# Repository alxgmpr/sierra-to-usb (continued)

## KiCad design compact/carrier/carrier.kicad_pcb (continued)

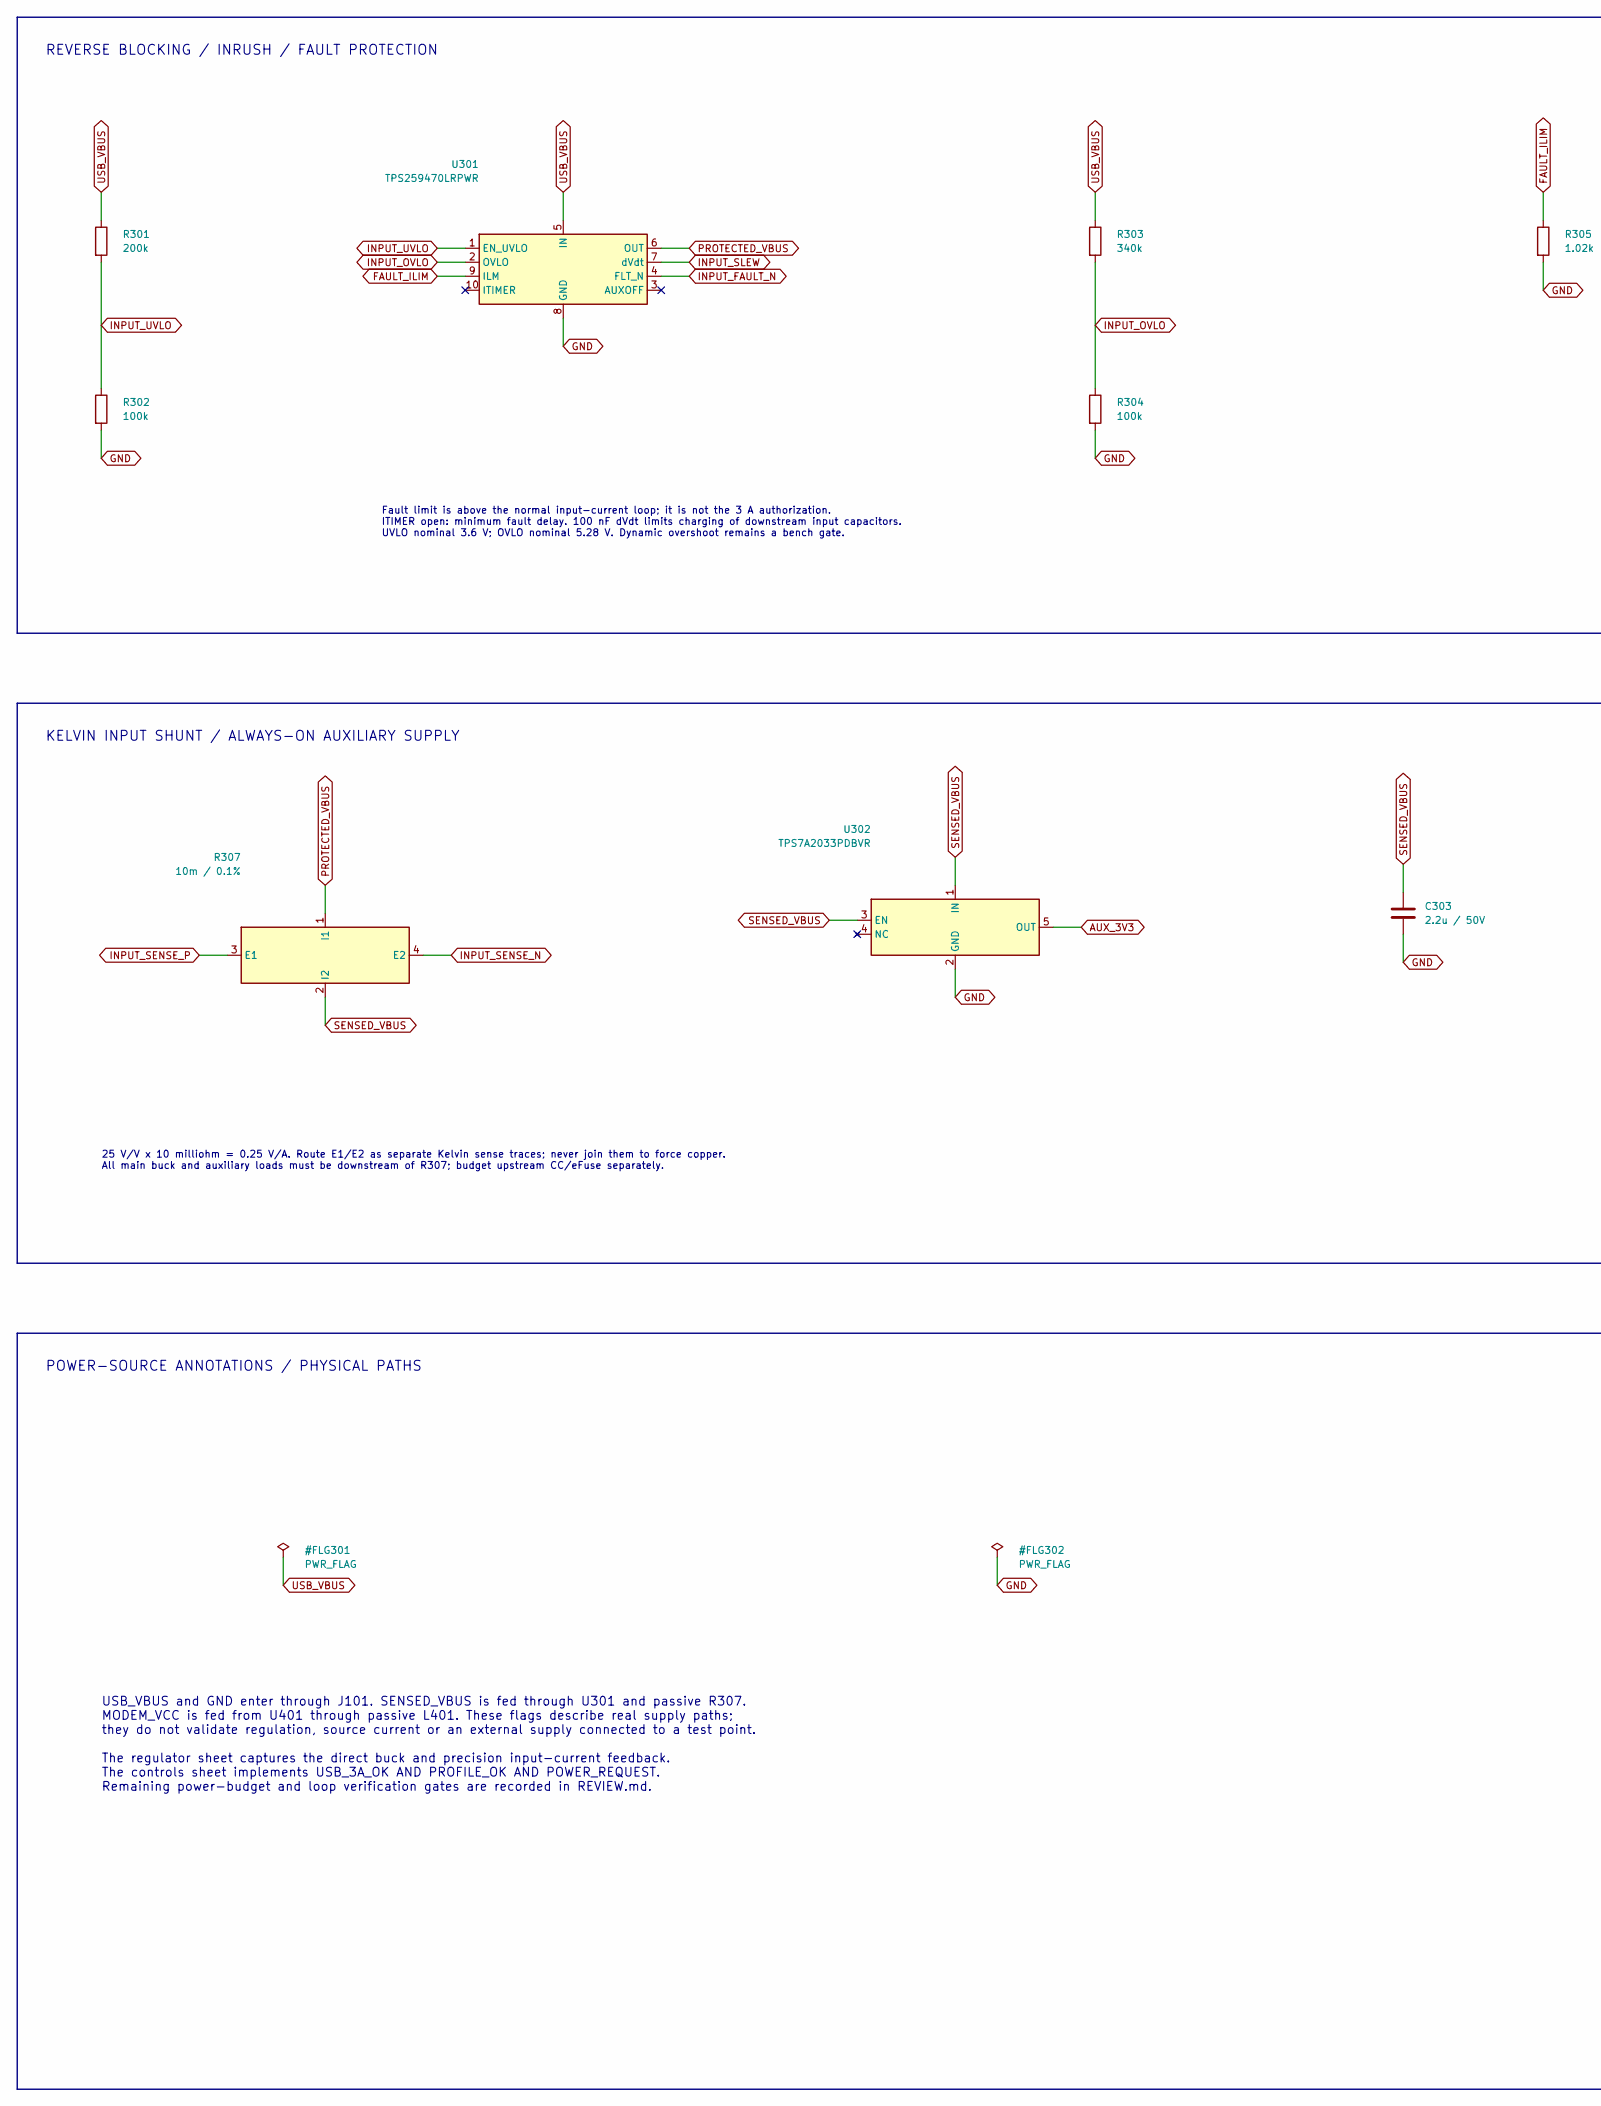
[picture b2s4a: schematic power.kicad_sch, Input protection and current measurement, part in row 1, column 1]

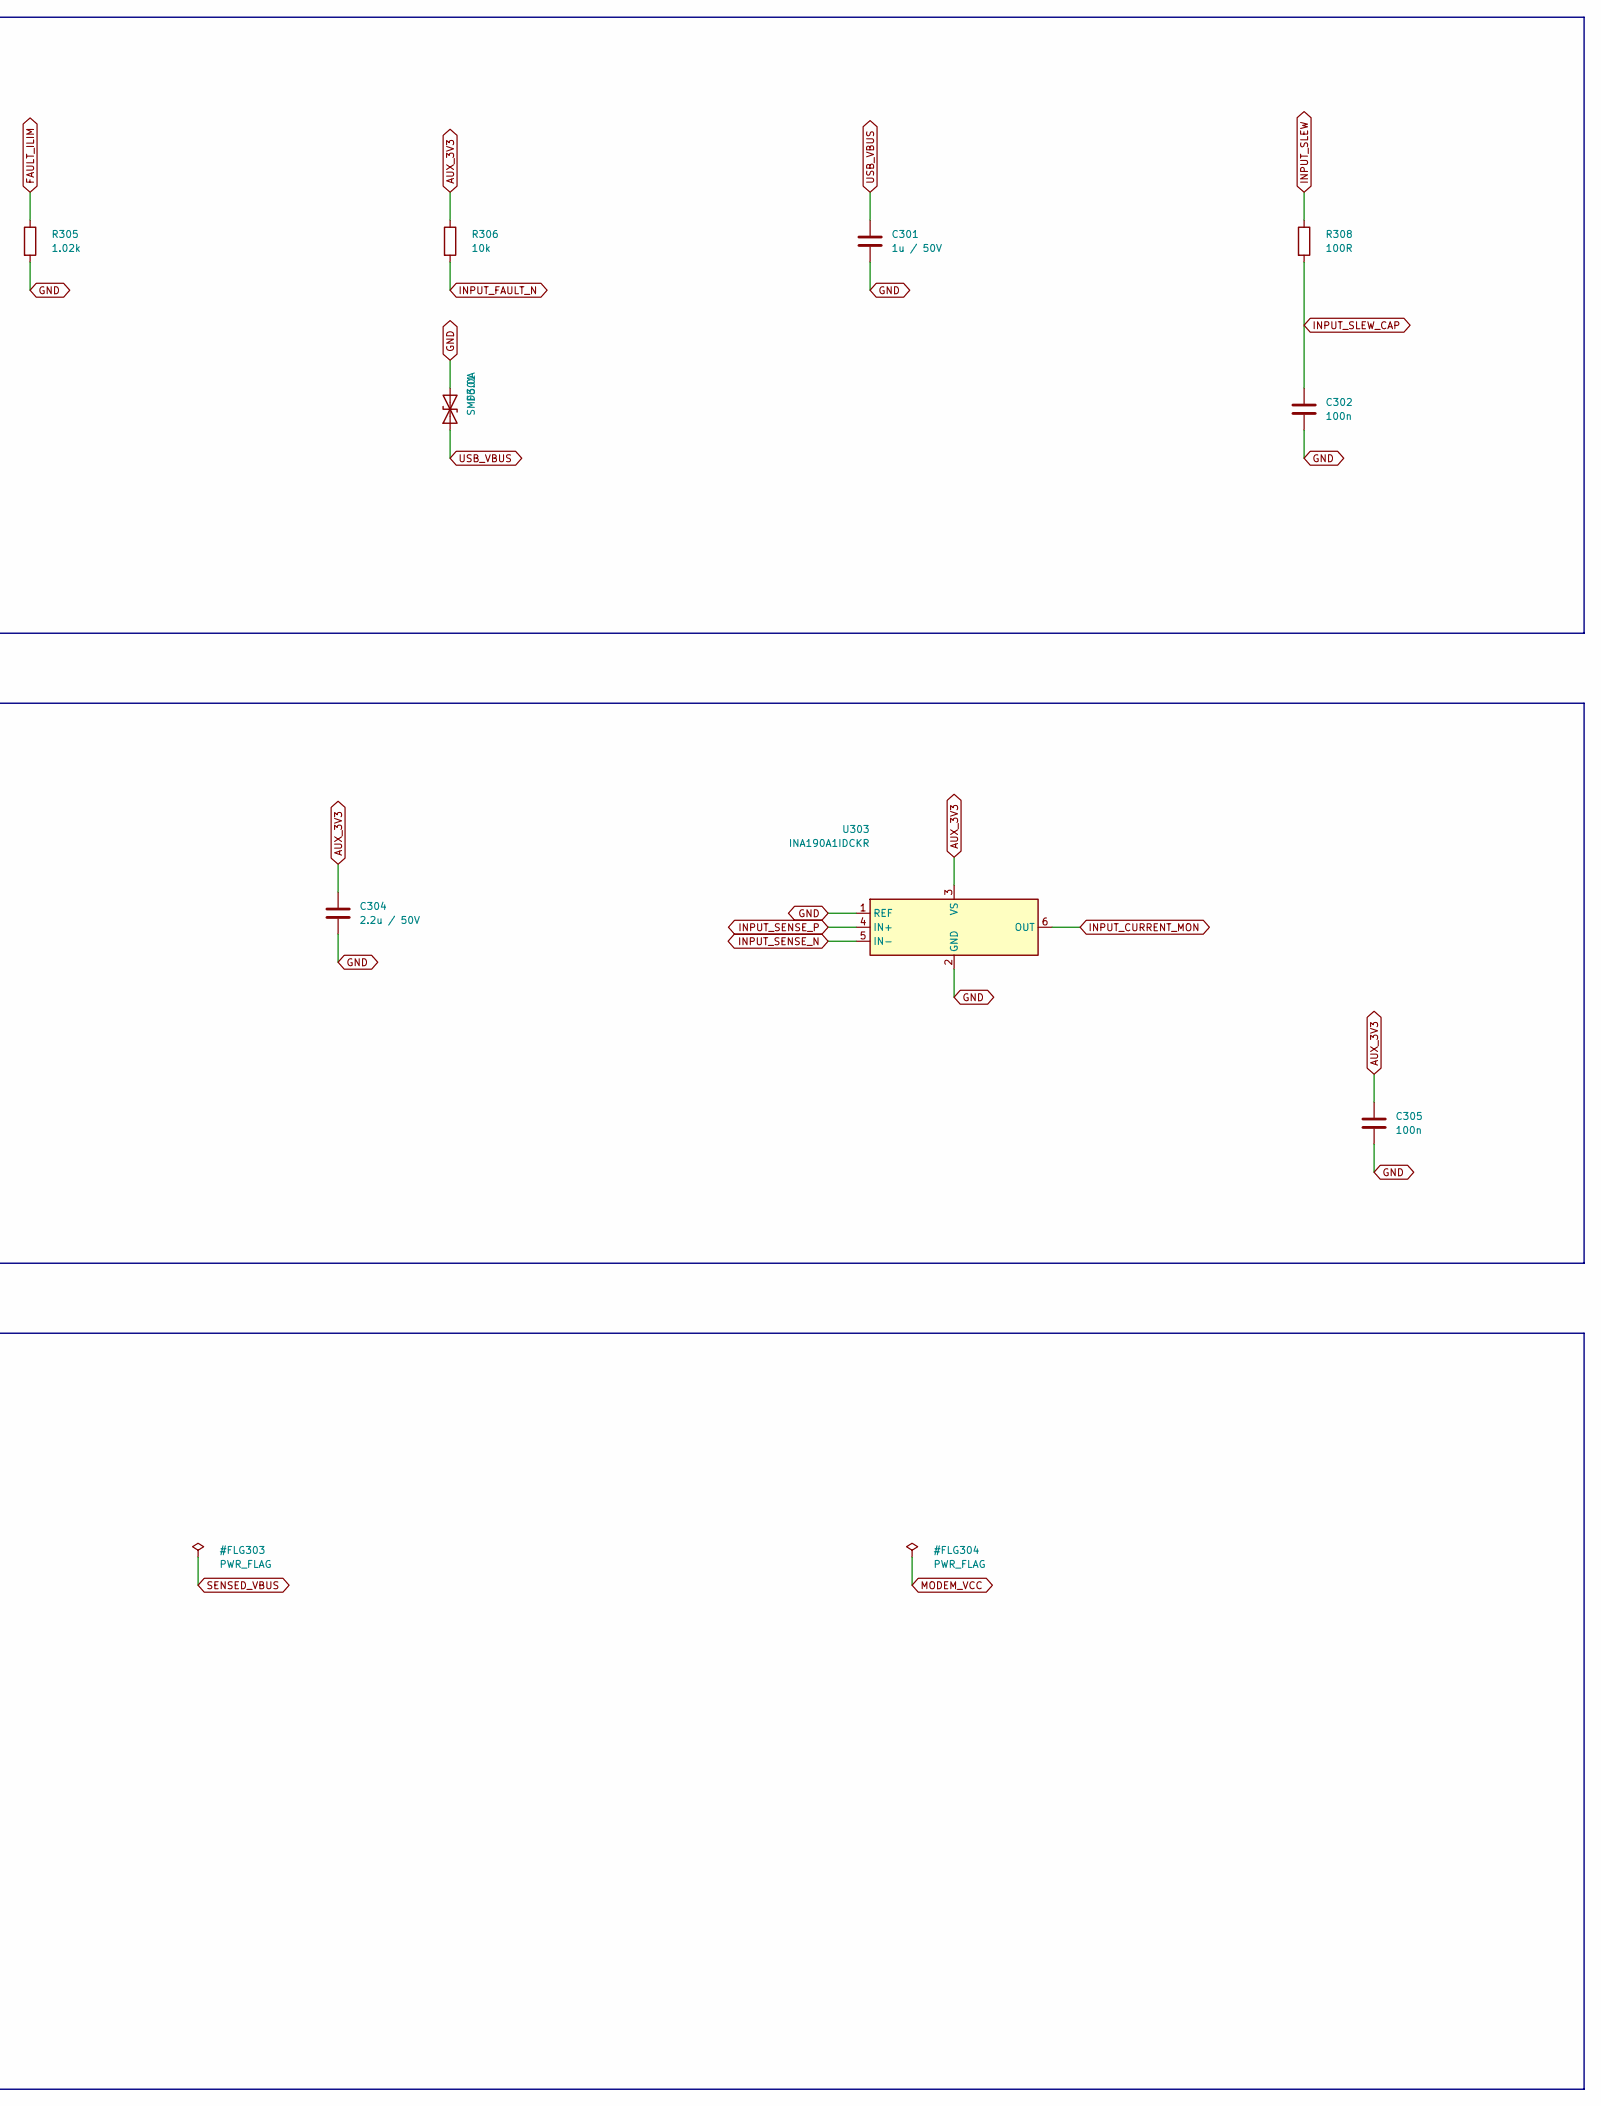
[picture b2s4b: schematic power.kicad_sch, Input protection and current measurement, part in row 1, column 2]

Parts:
C301: 1u / 50V; C_1206_3216Metric; MPN C3216X7R1H105K160AB
C302, C305: 100n; C_0805_2012Metric; MPN C2012X7R1H104K085AA
C303, C304: 2.2u / 50V; C_1206_3216Metric; MPN C3216X7R1H225K160AB
D301: SMF6.0A; Littelfuse_SMF_SOD123FL; MPN SMF6.0A
R301: 200k; R_0603_1608Metric; MPN ERJ-3EKF2003V
R302, R304: 100k; R_0603_1608Metric; MPN RC0603FR-07100KL
R303: 340k; R_0603_1608Metric; MPN RC0603FR-07340KL
R305: 1.02k; R_0603_1608Metric; MPN RC0603FR-071K02L
R306: 10k; R_0603_1608Metric; MPN RC0603FR-0710KL
R307: 10m / 0.1%; VPG_CSM2512_Kelvin; MPN Y14870R01000B9R
R308: 100R; R_0603_1608Metric; MPN RC0603FR-07100RL
U301: TPS259470LRPWR; TI_RPW0010A; MPN TPS259470LRPWR
U302: TPS7A2033PDBVR; SOT-23-5; MPN TPS7A2033PDBVR
U303: INA190A1IDCKR; SOT-363_SC-70-6; MPN INA190A1IDCKR

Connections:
AUX_3V3: C304.1, C305.1, R306.1, U302.5 (OUT), U303.3 (VS); also elsewhere on the board
FAULT_ILIM: R305.1, U301.9 (ILM)
GND: C301.2, C302.2, C303.2, C304.2, C305.2, D301.2 (A2), R302.2, R304.2, R305.2, U301.8 (GND), U302.2 (GND), U303.1 (REF), U303.2 (GND); also elsewhere on the board
INPUT_CURRENT_MON: U303.6 (OUT); also elsewhere on the board
INPUT_FAULT_N: R306.2, U301.4 (FLT_N)
INPUT_OVLO: R303.2, R304.1, U301.2 (OVLO)
INPUT_SENSE_N: R307.4 (E2), U303.5 (IN-)
INPUT_SENSE_P: R307.3 (E1), U303.4 (IN+)
INPUT_SLEW: R308.1, U301.7 (dVdt)
INPUT_SLEW_CAP: C302.1, R308.2
INPUT_UVLO: R301.2, R302.1, U301.1 (EN_UVLO)
PROTECTED_VBUS: R307.1 (I1), U301.6 (OUT)
SENSED_VBUS: C303.1, R307.2 (I2), U302.1 (IN), U302.3 (EN); also elsewhere on the board
USB_VBUS: C301.1, D301.1 (A1), R301.1, R303.1, U301.5 (IN); also elsewhere on the board

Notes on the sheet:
REVERSE BLOCKING / INRUSH / FAULT PROTECTION
Fault limit is above the normal input-current loop; it is not the 3 A authorization. ITIMER open: minimum fault delay. 100 nF dVdt limits charging of downstream input capacitors. UVLO nominal 3.6 V; OVLO nominal 5.28 V. Dynamic overshoot remains a bench gate.
KELVIN INPUT SHUNT / ALWAYS-ON AUXILIARY SUPPLY
25 V/V x 10 milliohm = 0.25 V/A. Route E1/E2 as separate Kelvin sense traces; never join them to force copper. All main buck and auxiliary loads must be downstream of R307; budget upstream CC/eFuse separately.
POWER-SOURCE ANNOTATIONS / PHYSICAL PATHS
USB_VBUS and GND enter through J101. SENSED_VBUS is fed through U301 and passive R307. MODEM_VCC is fed from U401 through passive L401. These flags describe real supply paths; they do not validate regulation, source current or an external supply connected to a test point. The regulator sheet captur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

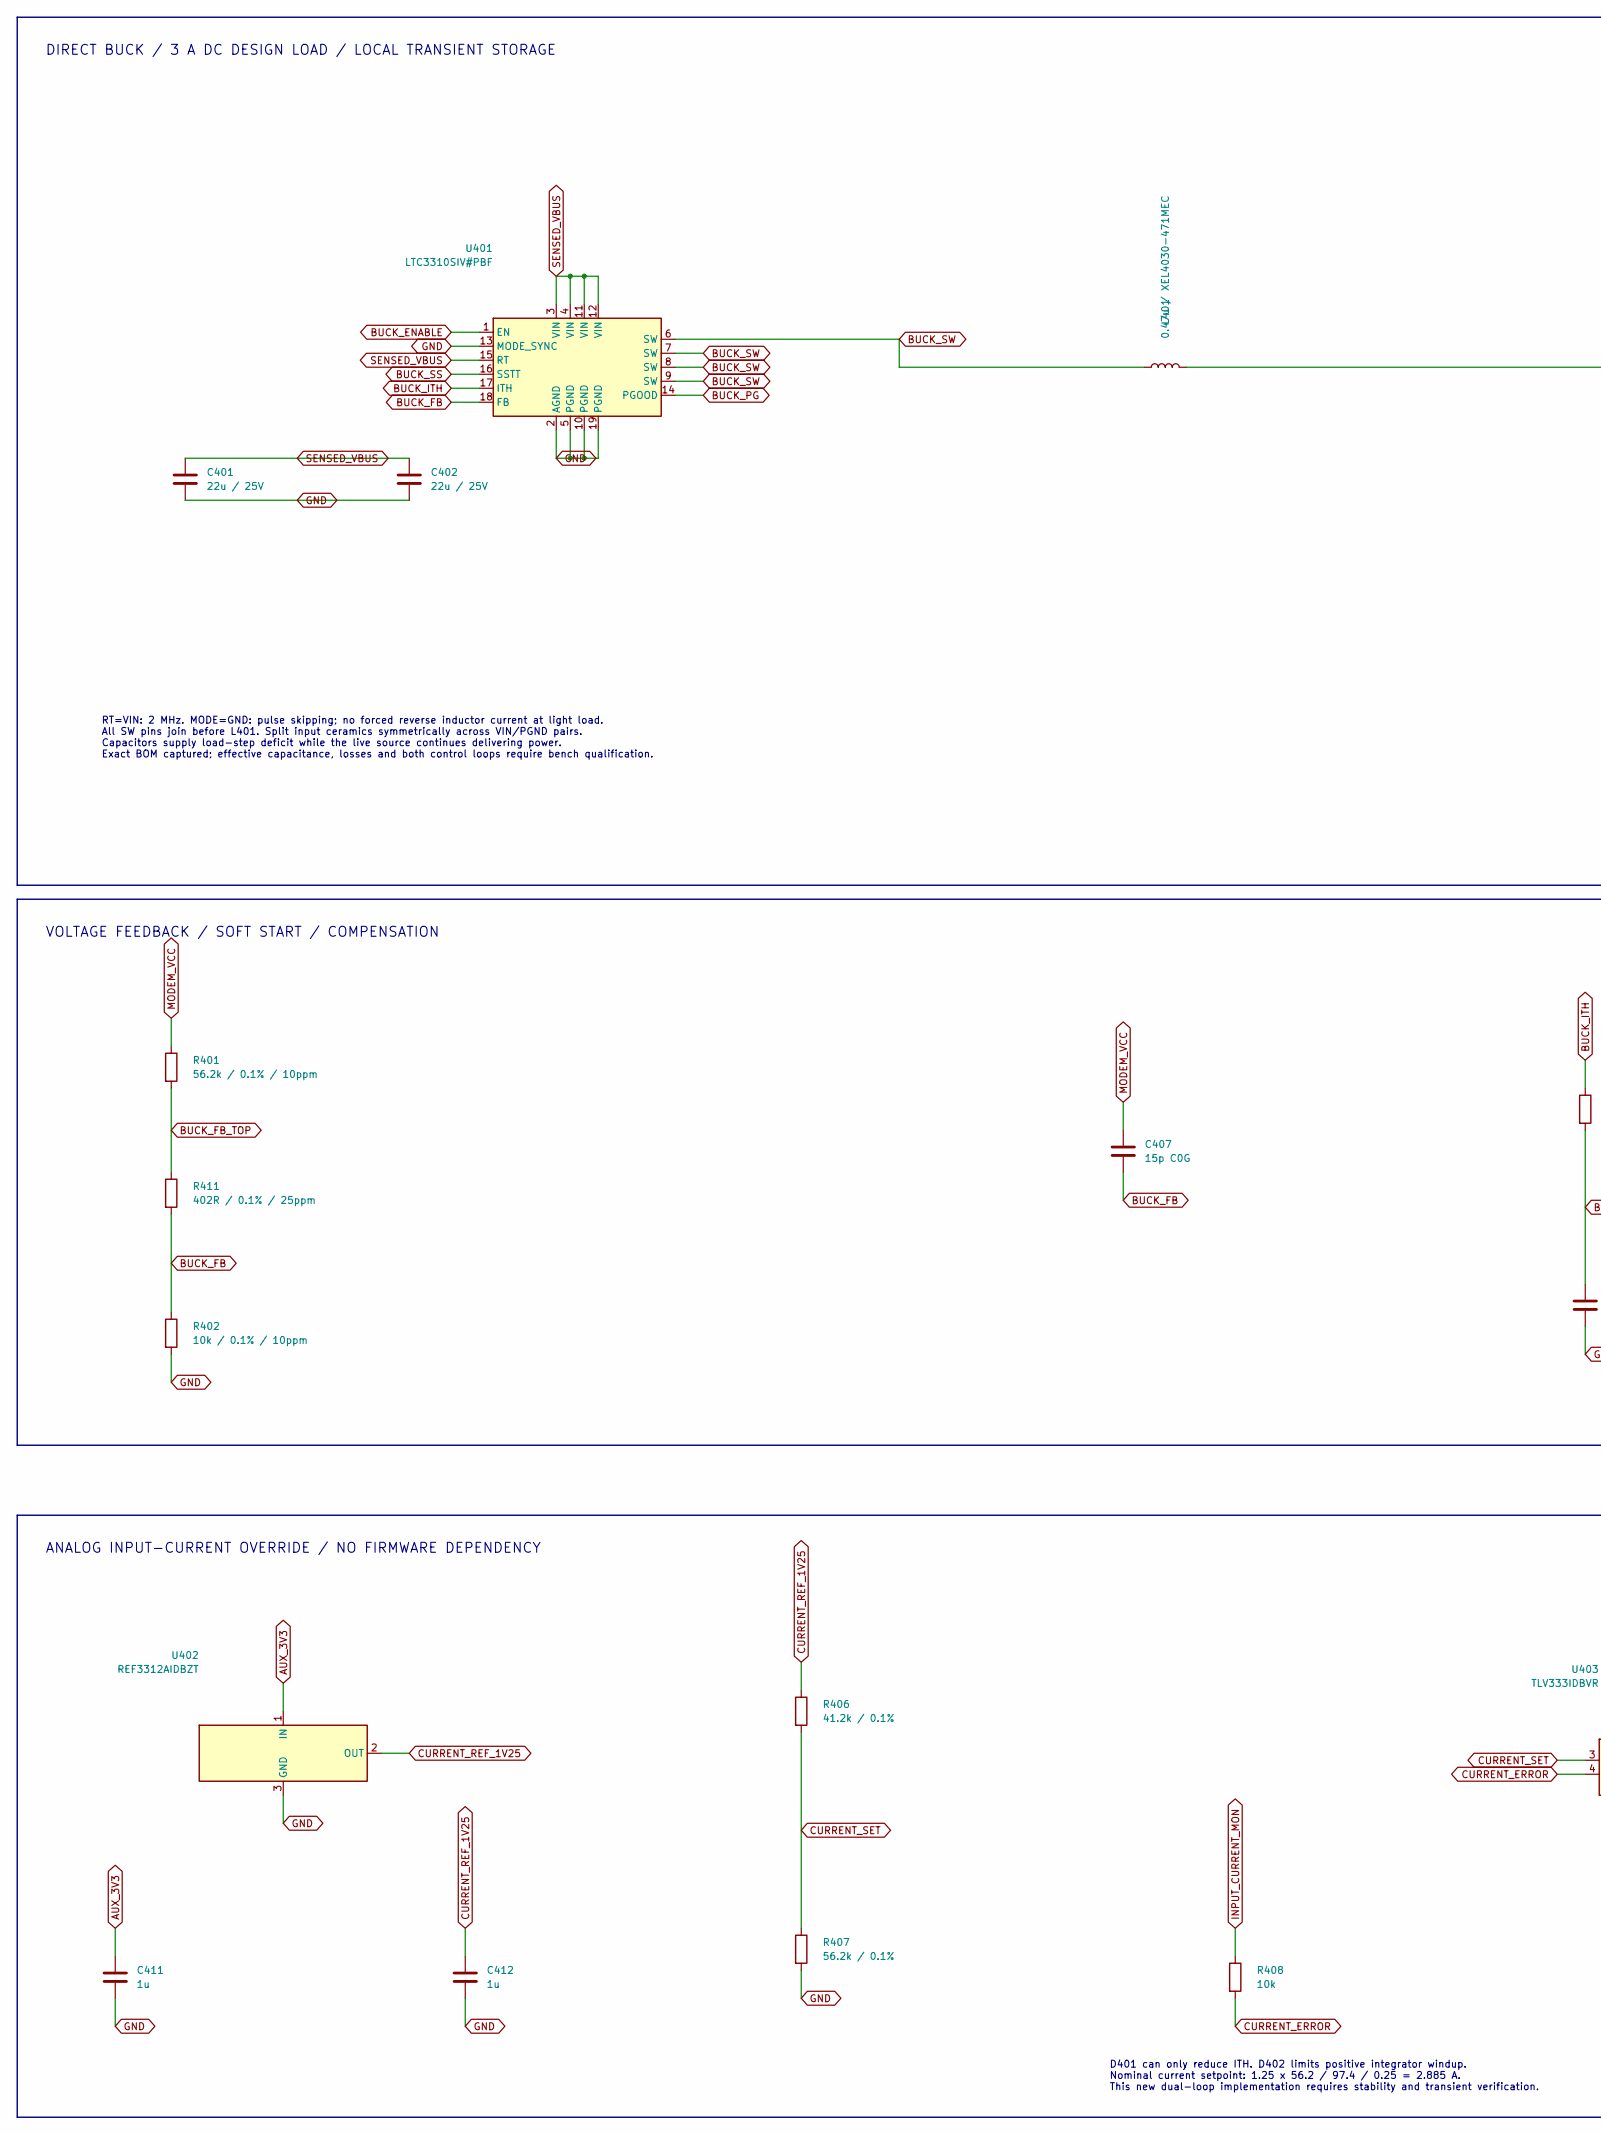
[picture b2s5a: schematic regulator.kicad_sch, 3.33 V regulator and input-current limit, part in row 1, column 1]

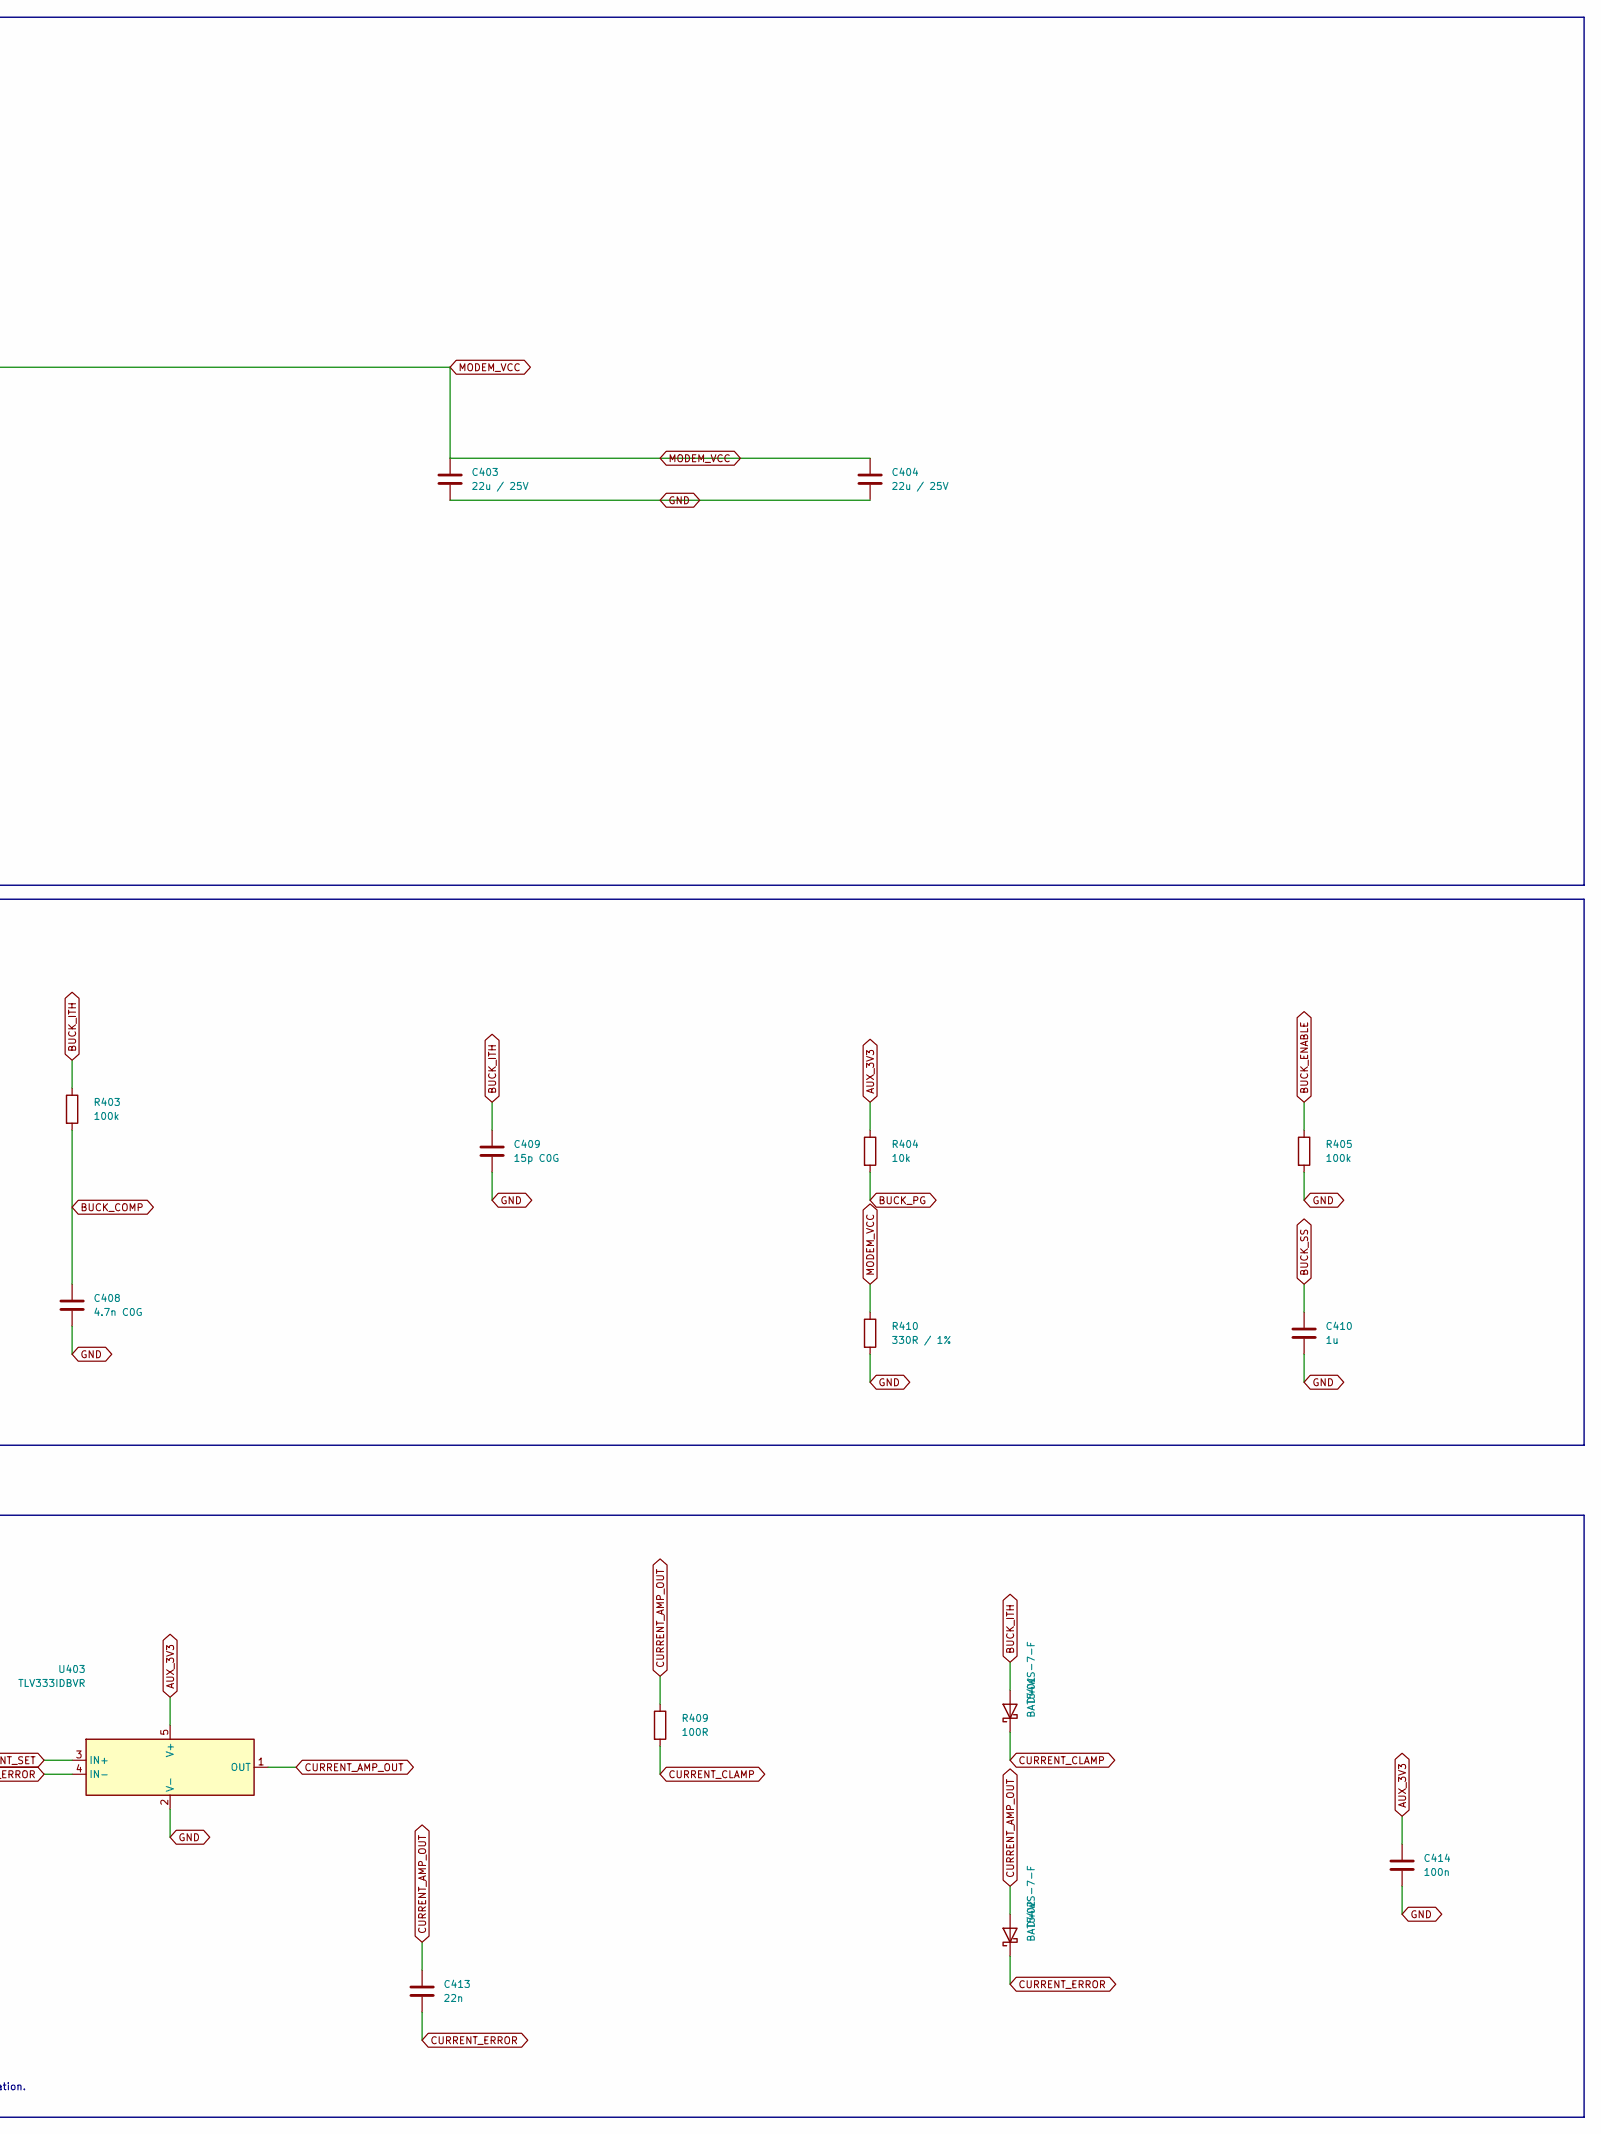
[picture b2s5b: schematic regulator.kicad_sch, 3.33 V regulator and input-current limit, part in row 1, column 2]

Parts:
C401, C402, C403, C404: 22u / 25V; C_1210_3225Metric; MPN C3225X7R1E226M250AB
C407, C409: 15p C0G; C_0805_2012Metric; MPN C0805C150J5GACTU
C408: 4.7n C0G; C_0805_2012Metric; MPN C2012C0G1H472J060AA
C410, C411, C412: 1u; C_1206_3216Metric; MPN C3216X7R1H105K160AB
C413: 22n; C_0805_2012Metric; MPN C0805C223J5GACTU
C414: 100n; C_0805_2012Metric; MPN C2012X7R1H104K085AA
D401, D402: BAT54WS-7-F; D_SOD-323; MPN BAT54WS-7-F
L401: 0.47u / XEL4030-471MEC; L_Coilcraft_XEL4030; MPN XEL4030-471MEC
R401: 56.2k / 0.1% / 10ppm; R_0603_1608Metric; MPN ERA-3ARB5622V
R402: 10k / 0.1% / 10ppm; R_0603_1608Metric; MPN ERA-3ARB103V
R403, R405: 100k; R_0603_1608Metric; MPN RC0603FR-07100KL
R404, R408: 10k; R_0603_1608Metric; MPN RC0603FR-0710KL
R406: 41.2k / 0.1%; R_0603_1608Metric; MPN RT0603BRD0741K2L
R407: 56.2k / 0.1%; R_0603_1608Metric; MPN RT0603BRD0756K2L
R409: 100R; R_0603_1608Metric; MPN RC0603FR-07100RL
R410: 330R / 1%; R_1206_3216Metric; MPN RC1206FR-07330RL
R411: 402R / 0.1% / 25ppm; R_0603_1608Metric; MPN RT0603BRD07402RL
U401: LTC3310SIV#PBF; LTC_LQFN18_3x3_05-08-1548; MPN LTC3310SIV#PBF
U402: REF3312AIDBZT; SOT-23; MPN REF3312AIDBZT
U403: TLV333IDBVR; SOT-23-5; MPN TLV333IDBVR

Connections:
AUX_3V3: C411.1, C414.1, R404.1, U402.1 (IN), U403.5 (V+); also elsewhere on the board
BUCK_COMP: C408.1, R403.2
BUCK_ENABLE: R405.1, U401.1 (EN); also elsewhere on the board
BUCK_FB: C407.2, R402.1, R411.2, U401.18 (FB)
BUCK_FB_TOP: R401.2, R411.1
BUCK_ITH: C409.1, D401.2 (A), R403.1, U401.17 (ITH); also elsewhere on the board
BUCK_PG: R404.2, U401.14 (PGOOD)
BUCK_SS: C410.1, U401.16 (SSTT)
BUCK_SW: L401.1, U401.6 (SW), U401.7 (SW), U401.8 (SW), U401.9 (SW)
CURRENT_AMP_OUT: C413.1, D402.2 (A), R409.1, U403.1 (OUT)
CURRENT_CLAMP: D401.1 (K), R409.2
CURRENT_ERROR: C413.2, D402.1 (K), R408.2, U403.4 (IN-)
CURRENT_REF_1V25: C412.1, R406.1, U402.2 (OUT)
CURRENT_SET: R406.2, R407.1, U403.3 (IN+)
GND: C401.2, C402.2, C403.2, C404.2, C408.2, C409.2, C410.2, C411.2, C412.2, C414.2, R402.2, R405.2, R407.2, R410.2, U401.2 (AGND), U401.5 (PGND), U401.10 (PGND), U401.13 (MODE_SYNC), U401.19 (PGND), U402.3 (GND), U403.2 (V-); also elsewhere on the board
INPUT_CURRENT_MON: R408.1; also elsewhere on the board
MODEM_VCC: C403.1, C404.1, C407.1, L401.2, R401.1, R410.1; also elsewhere on the board
SENSED_VBUS: C401.1, C402.1, U401.3 (VIN), U401.4 (VIN), U401.11 (VIN), U401.12 (VIN), U401.15 (RT); also elsewhere on the board

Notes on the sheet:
DIRECT BUCK / 3 A DC DESIGN LOAD / LOCAL TRANSIENT STORAGE
RT=VIN: 2 MHz. MODE=GND: pulse skipping; no forced reverse inductor current at light load. All SW pins join before L401. Split input ceramics symmetrically across VIN/PGND pairs. Capacitors supply load-step deficit while the live source continues delivering power. Exact BOM captured; effective capa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
VOLTAGE FEEDBACK / SOFT START / COMPENSATION
ANALOG INPUT-CURRENT OVERRIDE / NO FIRMWARE DEPENDENCY
D401 can only reduce ITH. D402 limits positive integrator windup. Nominal current setpoint: 1.25 x 56.2 / 97.4 / 0.25 = 2.885 A. This new dual-loop implementation requires stability and transient verification.
